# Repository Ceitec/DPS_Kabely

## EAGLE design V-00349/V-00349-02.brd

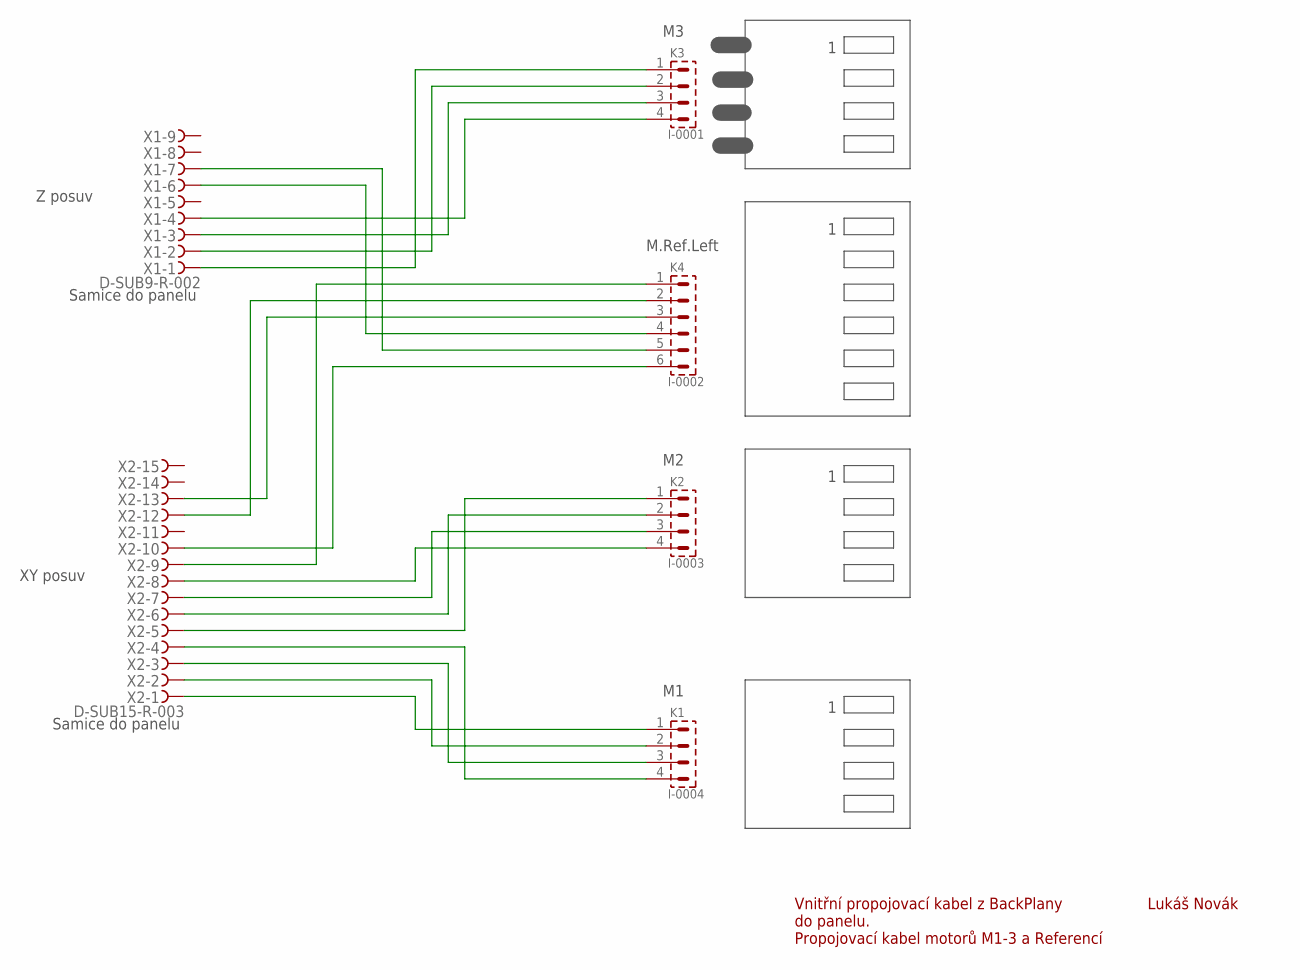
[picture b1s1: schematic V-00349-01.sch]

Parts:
K1: I-0004; PSH02-04P
K2: I-0003; PSH02-04P
K3: I-0001; PSH02-04P
K4: I-0002; PSH02-06P
X1: D-SUB9-R-002; H2M09ST
X2: D-SUB15-R-003; H2M15ST

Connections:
unnamed: K3.1, X1.1
unnamed: K3.2, X1.2
unnamed: K3.3, X1.3
unnamed: K3.4, X1.4
unnamed: K4.1, X2.9
unnamed: K4.2, X2.12
unnamed: K4.3, X2.13
unnamed: K4.4, X1.6
unnamed: K4.5, X1.7
unnamed: K4.6, X2.10
unnamed: K1.1, X2.1
unnamed: K1.2, X2.2
unnamed: K1.3, X2.3
unnamed: K1.4, X2.4
unnamed: K2.1, X2.5
unnamed: K2.2, X2.6
unnamed: K2.3, X2.7
unnamed: K2.4, X2.8

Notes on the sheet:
M.Ref.Left
Samice do panelu
Lukáš Novák
Vnitřní propojovací kabel z BackPlany do panelu. Propojovací kabel motorů M1-3 a Referencí
Z posuv
XY posuv

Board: 2 copper layers, 6 parts (0 on the bottom side), 18 nets, no tracks yet.

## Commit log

2015-08-11 :octocat: Added .gitattributes & .gitignore files
2015-08-11 Prvotní verze
2015-08-11 Pridani zakazanych koncovek
2015-09-25 A
    A
2015-11-22 Nove kabely a seznam jejich
2015-11-30 Krabicka
2016-02-10 v2.0.0

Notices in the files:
parts and their libraries:
Copyright (C) PaJa 2011-2014
